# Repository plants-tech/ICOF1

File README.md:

ICOF1

Integrated RP2040 Circuit Open Frame 1 PCB Design

utilizes default haybox and pico-rectangle pinout

big thanks to Cubs, Quark, Bjart, and Greggy Turbo

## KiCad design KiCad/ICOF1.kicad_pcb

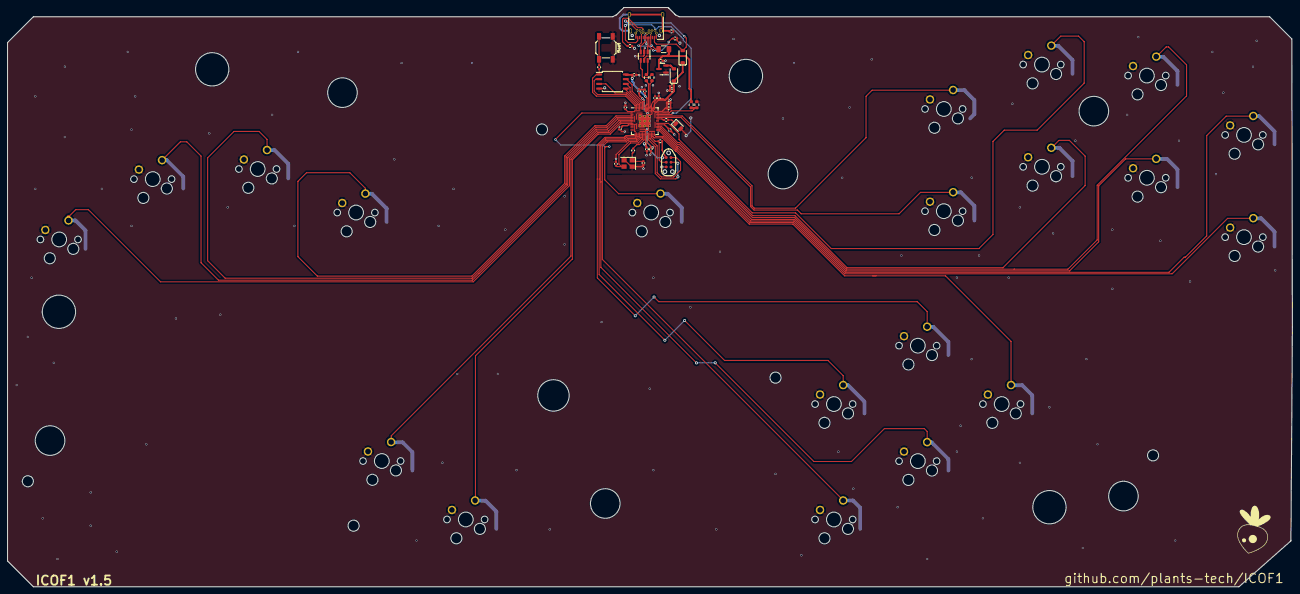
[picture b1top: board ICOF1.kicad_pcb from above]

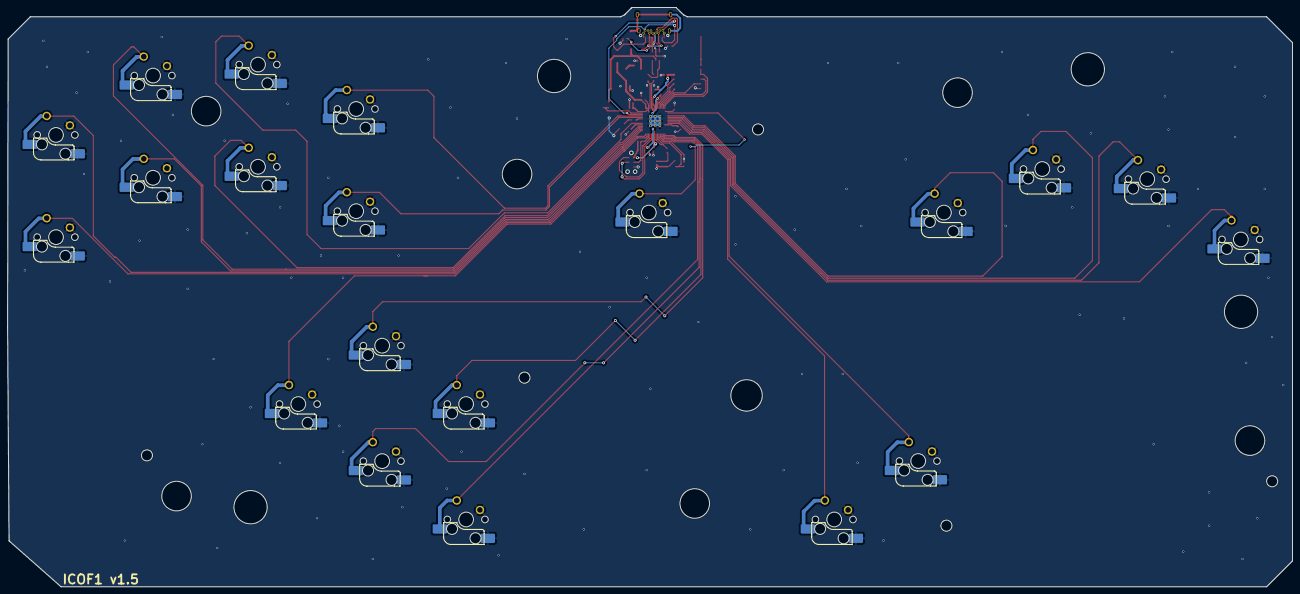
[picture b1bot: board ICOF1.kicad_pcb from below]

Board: 2 copper layers, 347.1 x 156.5 mm, 76 parts (20 on the bottom side), 53 nets.

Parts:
@HOLE0, @HOLE1, @HOLE2, @HOLE3, @HOLE4, @HOLE5, @HOLE6, @HOLE7, @HOLE8, @HOLE9, @HOLE10, @HOLE11, @HOLE12, @HOLE13, @HOLE14, @HOLE15: (no value)
C1, C2, C4, C10: 1uF; C_0402_1005Metric
C3, C5, C6, C11, C12, C13, C14, C15, C16, C17: 100nF; C_0402_1005Metric
C7, C8: 22pF; C_0402_1005Metric
C9: 10uF; C_0402_1005Metric
D1, D2: Schottky Diode; CUSTOM D_SOD-123
D3: Green_LED; LED_0805_2012Metric
F1: 500 mA; Fuse_1206_3216Metric
G: LOGO
J1: USB C Connector; TYPE-C_24P_QCHT
J2: Tag-Connect TC2030; CON_TC2030_outlined
R1: 10k; R_0402_1005Metric
R2, R3: 5.1k; R_0402_1005Metric
R4: 470; R_0402_1005Metric
R5: 5.6k; R_0603_1608Metric
R6: 10k; R_0603_1608Metric
R8, R9: 27; R_0603_1608Metric
R10, R11: 1k; R_0402_1005Metric
SW1: Boot; SW_SPST_SKQG_WithStem
SW3: Start; SW_MX_HS_1u_Htangl
SW4: L; SW_MX_HS_1u_Htangl
SW6: Left; SW_MX_HS_1u_Htangl
SW8: Down; SW_MX_HS_1u_Htangl
SW10: Right; SW_MX_HS_1u_Htangl
SW12: R; SW_MX_HS_1u_Htangl
SW14: Y; SW_MX_HS_1u_Htangl
SW17: LS; SW_MX_HS_1u_Htangl
SW19: MS; SW_MX_HS_1u_Htangl
SW21: B; SW_MX_HS_1u_Htangl
SW22: X; SW_MX_HS_1u_Htangl
SW25: Z; SW_MX_HS_1u_Htangl
SW26: UP; SW_MX_HS_1u_Htangl
SW28: M1; SW_MX_HS_1u_Htangl
SW30: M2; SW_MX_HS_1u_Htangl
SW32: C_LT; SW_MX_HS_1u_Htangl
SW35: C_UP; SW_MX_HS_1u_Htangl
SW36: C_DN; SW_MX_HS_1u_Htangl
SW38: A; SW_MX_HS_1u_Htangl
SW40: C_RT; SW_MX_HS_1u_Htangl
U1: XC6206; SOT-23
U2: USBLC6-2SC6; SOT-23-6
U3: RP2040; RP2040-QFN-56
U4: W25Q128JVS; SOIC-8_5.23x5.23mm_P1.27mm
Y1: 12MHz; Crystal_SMD_3225-4Pin_3.2x2.5mm

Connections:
3vCable: D2.2 (A), J1.A2 (TX1+), J1.B2 (TX2+)
+1V1: C4.1, C5.1, C6.1, U3.23 (DVDD), U3.45 (VREG_VOUT), U3.50 (DVDD)
+3V3: C1.2, C3.1, C9.1, C10.1, C11.1, C12.1, C13.1, C14.1, C15.1, C16.1, C17.1, D1.1 (K), D2.1 (K), J2.1, U3.1 (IOVDD), U3.10 (IOVDD), U3.22 (IOVDD), U3.33 (IOVDD), U3.42 (IOVDD), U3.43 (ADC_AVDD), U3.44 (VREG_VIN), U3.48 (USB_VDD), U3.49 (IOVDD), U4.8 (VCC)
+5V: C2.2, F1.2, R5.1, U1.3 (VI), U2.5 (VBUS)
/D_+: R8.2, U3.47 (D+)
/D_-: R9.2, U3.46 (D-)
/XTAL_O: C8.2, R11.1, Y1.1
/~USB_BOOT: R10.1, SW1.2
A: SW38.1, U3.17 (GPIO14)
B: SW21.1, U3.38 (GPIO26/ADC0)
CS: R10.2, U3.56 (QSPI_SS_N), U4.1 (~CS)
C_DN: SW36.1, U3.18 (GPIO15)
C_LT: SW32.1, U3.16 (GPIO13)
C_RT: SW40.1, U3.27 (GPIO16)
C_UP: SW35.1, U3.15 (GPIO12)
D+: R8.1, U2.6 (I/O1)
D-: R9.1, U2.4 (I/O2)
DATA: J1.A11 (RX2+), J1.B11 (RX1+), U3.40 (GPIO28/ADC2)
DBUS+: J1.A6 (D+), J1.B6 (D+), U2.1 (I/O1)
DBUS-: J1.A7 (D-), J1.B7 (D-), U2.3 (I/O2)
DOWN: SW8.1, U3.5 (GPIO3)
GND: C1.1, C2.1, C3.2, C4.2, C5.2, C6.2, C7.1, C8.1, C9.2, C10.2, C11.2, C12.2, C13.2, C14.2, C15.2, C16.2, C17.2, D3.2, J1.A1 (GND), J1.A12 (GND), J1.B1 (GND), J1.B12 (GND), J2.5, R1.2, R2.1, R3.2, R6.2, SW1.1, SW3.2, SW4.2, SW6.2, SW8.2, SW10.2, SW12.2, SW14.2, SW17.2, SW19.2, SW21.2, SW22.2, SW25.2, SW26.2, SW28.2, SW30.2, SW32.2, SW35.2, SW36.2, SW38.2, SW40.2, U1.1 (GND), U2.2 (GND), U3.19 (TESTEN), U3.57 (GND), U4.4 (GND), Y1.2, Y1.4
L: SW4.1, U3.7 (GPIO5)
LEFT: SW6.1, U3.6 (GPIO4)
LS: SW17.1, U3.31 (GPIO20)
M1: SW28.1, U3.8 (GPIO6)
M2: SW30.1, U3.9 (GPIO7)
MS: SW19.1, U3.29 (GPIO18)
unnamed: D1.2 (A), U1.2 (VO)
unnamed: D3.1, R4.2
unnamed: F1.1, J1.A4 (VBUS), J1.A9 (VBUS), J1.B4 (VBUS), J1.B9 (VBUS)
unnamed: J1.A5 (CC1), R3.1
unnamed: J1.B5 (CC2), R2.2
unnamed: J1.S1 (SHIELD), R1.1
PICO_LED: R4.1, U3.37 (GPIO25)
QSPI_CLK: U3.52 (QSPI_SCLK), U4.6 (CLK)
R: SW12.1, U3.39 (GPIO27/ADC1)
RIGHT: SW10.1, U3.4 (GPIO2)
SD0: U3.53 (QSPI_SD0), U4.5 (DI(IO0))
SD1: U3.55 (QSPI_SD1), U4.2 (DO(IO1))
SD2: U3.54 (QSPI_SD2), U4.3 (IO2)
SD3: U3.51 (QSPI_SD3), U4.7 (IO3)
START: SW3.1, U3.2 (GPIO0)
SWCLK: J2.4, U3.24 (SWCLK)
SWD: J2.2, U3.25 (SWDIO)
UP: SW26.1, U3.28 (GPIO17)
VBUS_SENSE: R5.2, R6.1, U3.41 (GPIO29/ADC3)
X: SW22.1, U3.32 (GPIO21)
XTAL_IN: C7.2, U3.20 (XTAL_IN), Y1.3
XTAL_OUT: R11.2, U3.21 (XTAL_OUT)
Y: SW14.1, U3.34 (GPIO22)
Z: SW25.1, U3.30 (GPIO19)
~RESET: J2.3, U3.26 (~RUN)

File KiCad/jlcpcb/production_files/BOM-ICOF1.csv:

Comment,Designator,Footprint,LCSC
1k,"R10,R11",R_0402_1005Metric,C11702
Schottky Diode,"D1,D2",CUSTOM D_SOD-123,C130880
100nF,"C11,C12,C13,C14,C15,C16,C17,C3,C5,C6",C_0402_1005Metric,C1525
10uF,C9,C_0402_1005Metric,C15525
22pF,"C7,C8",C_0402_1005Metric,C1555
RP2040,U3,RP2040-QFN-56,C2040
5.6k,R5,R_0603_1608Metric,C23189
470,R4,R_0402_1005Metric,C25167
27,"R8,R9",R_0603_1608Metric,C25190
10k,"R1,R2,R3",R_0402_1005Metric,C25744
10k,R6,R_0603_1608Metric,C25804
Green_LED,D3,LED_0805_2012Metric,C434435
USB C Connector,J1,TYPE-C_24P_QCHT,C456013
Boot,SW1,SW_SPST_SKQG_WithStem,C5156480
1uF,"C1,C10,C2,C4",C_0402_1005Metric,C52923
XC6206,U1,SOT-23,C5446
USBLC6-2SC6,U2,SOT-23-6,C7519
500 mA,F1,Fuse_1206_3216Metric,C883125
12MHz,Y1,Crystal_SMD_3225-4Pin_3.2x2.5mm,C9002
W25Q128JVS,U4,SOIC-8_5.23x5.23mm_P1.27mm,C97521

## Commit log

2023-02-26 first
2023-03-04 donev1
2023-03-04 v1 !
    cleaned up and done yay
2023-03-04 v1.1 lol
2023-03-15 v1.2!
2023-03-24 ayo!
2023-05-17 fixed L and R, corrected sch pinout
2023-05-17 cleaned up folders, added firmware
2023-05-17 v1.4
2023-05-20 final
2023-05-22 final final v1.2
2023-05-28 Update github-metrics.svg - [Skip GitHub Action]
2023-05-28 Revert "Create main.yml"
    This reverts commit 791235269700674157468ce497b1f3eabb45a812.
2023-06-12 v1.5
2023-06-16 expanded thru-holes for 5 pin keyswitches
2023-06-27 ICOF1_v1.5
    ready for publish
